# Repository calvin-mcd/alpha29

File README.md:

# alpha29

alpha29 (or mini planck) is a riff on the amazing [alpha28](https://github.com/PyrooL/Alpha) by PyrooL. This project was more of an exercise and is consider finished.

## Layout

[Link](https://www.keyboard-layout-editor.com/#/gists/f35a5c950e0317b4dc41fa3c3aa06123)

##RGB

Because this board uses a rp2040, you will need to use a logic shifter to utilise the rgb breakout. Something like [this](https://learn.sparkfun.com/tutorials/retired---using-the-logic-level-converter) or [this](https://learn.sparkfun.com/tutorials/bi-directional-logic-level-converter-hookup-guide) for example.

## Todo
- [ ] create firmware
- [ ] create case

## Disclaimer

Please note that this project is a work in progress with no guarantees of a working outcome. No-one involved in this project is responsible for any usage issues that may arise. However, feel free to edit, modify and otherwise utilise these files.

## License

This project is released under the GPL v3 License. Please refer to the LICENCE file.
  
## Credits

huge thanks to Pyrool for the inspiration.
  
Any questions, contact Calvin0563 on Discord.

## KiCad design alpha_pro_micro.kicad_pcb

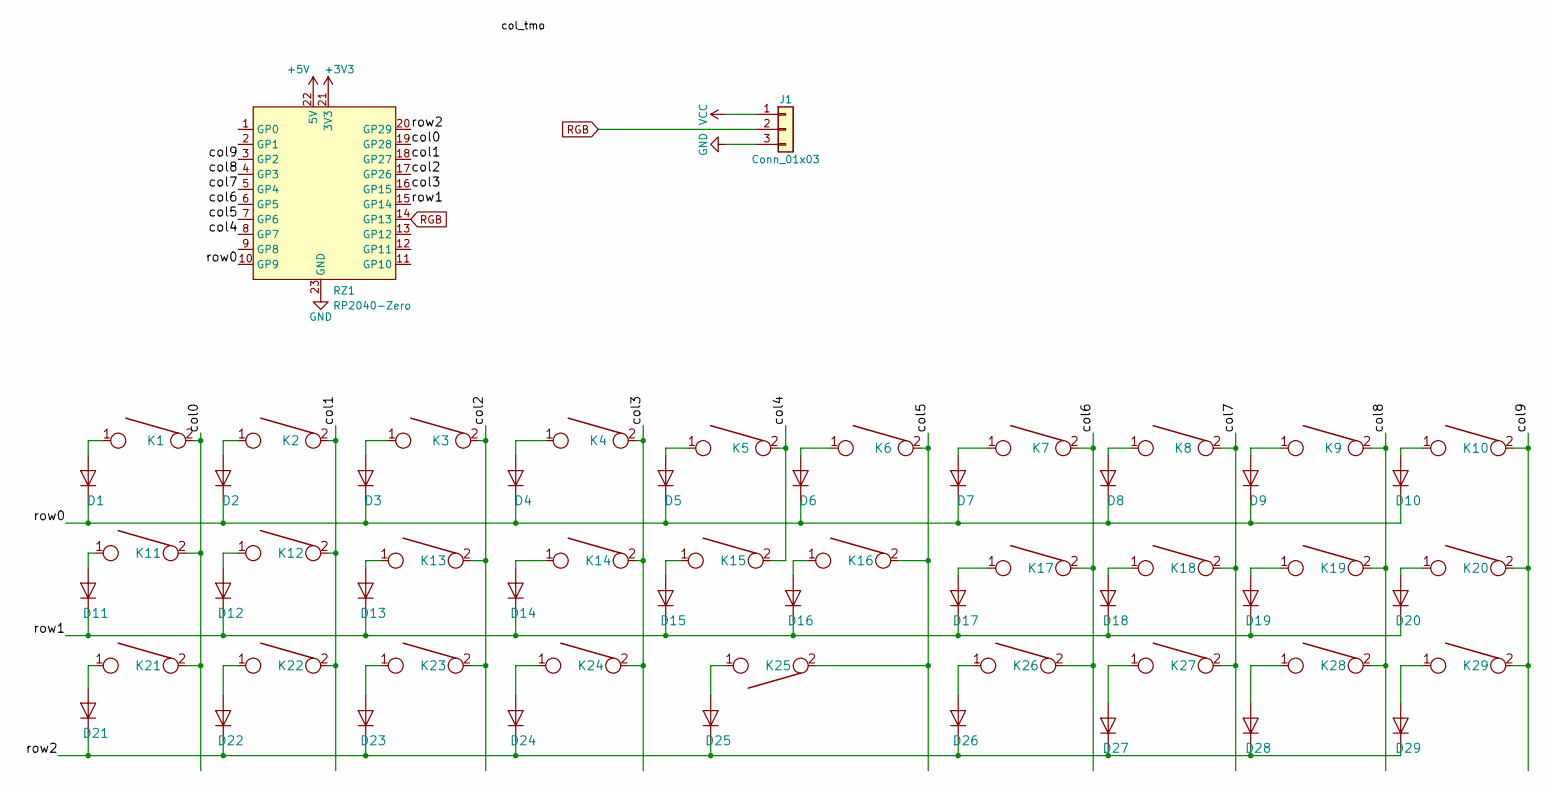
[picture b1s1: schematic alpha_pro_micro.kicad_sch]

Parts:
D1, D2, D3, D4, D5, D6, D7, D8, D9, D10, D11, D12, D13, D14, D15, D16, D17, D18, D19, D20, D21, D22, D23, D24, D25, D26, D27, D28, D29: D; ComboDiode
J1: Conn_01x03; Pin_Header_Straight_1x03_Pitch2.54mm
K1, K2, K3, K4, K5, K6, K7, K8, K9, K10, K11, K12, K13, K14, K15, K16, K17, K18, K19, K20, K21, K22, K23, K24, K26, K27, K28, K29: KEYSW; MXOnly-1U-NoLED
K25: KEYSW; MXOnly-2U-ReversedStabilizers-NoLED
RZ1: RP2040-Zero

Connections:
+3V3: RZ1.21 (3V3)
+5V: RZ1.22 (5V)
/col0: K1.2, K11.2, K21.2, RZ1.19 (GP28)
/col1: K2.2, K12.2, K22.2, RZ1.18 (GP27)
/col2: K3.2, K13.2, K23.2, RZ1.17 (GP26)
/col3: K4.2, K14.2, K24.2, RZ1.16 (GP15)
/col4: K5.2, K15.2, RZ1.8 (GP7)
/col5: K6.2, K16.2, K25.2, RZ1.7 (GP6)
/col6: K7.2, K17.2, K26.2, RZ1.6 (GP5)
/col7: K8.2, K18.2, K27.2, RZ1.5 (GP4)
/col8: K9.2, K19.2, K28.2, RZ1.4 (GP3)
/col9: K10.2, K20.2, K29.2, RZ1.3 (GP2)
/row0: D1.1 (K), D2.1 (K), D3.1 (K), D4.1 (K), D5.1 (K), D6.1 (K), D7.1 (K), D8.1 (K), D9.1 (K), D10.1 (K), RZ1.10 (GP9)
/row1: D11.1 (K), D12.1 (K), D13.1 (K), D14.1 (K), D15.1 (K), D16.1 (K), D17.1 (K), D18.1 (K), D19.1 (K), D20.1 (K), RZ1.15 (GP14)
/row2: D21.1 (K), D22.1 (K), D23.1 (K), D24.1 (K), D25.1 (K), D26.1 (K), D27.1 (K), D28.1 (K), D29.1 (K), RZ1.20 (GP29)
GND: J1.3, RZ1.23 (GND)
unnamed: D1.2 (A), K1.1
unnamed: D2.2 (A), K2.1
unnamed: D3.2 (A), K3.1
unnamed: D4.2 (A), K4.1
unnamed: D5.2 (A), K5.1
unnamed: D6.2 (A), K6.1
unnamed: D7.2 (A), K7.1
unnamed: D8.2 (A), K8.1
unnamed: D9.2 (A), K9.1
unnamed: D10.2 (A), K10.1
unnamed: D11.2 (A), K11.1
unnamed: D12.2 (A), K12.1
unnamed: D13.2 (A), K13.1
unnamed: D14.2 (A), K14.1
unnamed: D15.2 (A), K15.1
unnamed: D16.2 (A), K16.1
unnamed: D17.2 (A), K17.1
unnamed: D18.2 (A), K18.1
unnamed: D19.2 (A), K19.1
unnamed: D20.2 (A), K20.1
unnamed: D21.2 (A), K21.1
unnamed: D22.2 (A), K22.1
unnamed: D23.2 (A), K23.1
unnamed: D24.2 (A), K24.1
unnamed: D26.2 (A), K26.1
unnamed: D27.2 (A), K27.1
unnamed: D28.2 (A), K28.1
unnamed: D29.2 (A), K29.1
unnamed: D25.2 (A), K25.1
RGB: J1.2, RZ1.14 (GP13)
VCC: J1.1

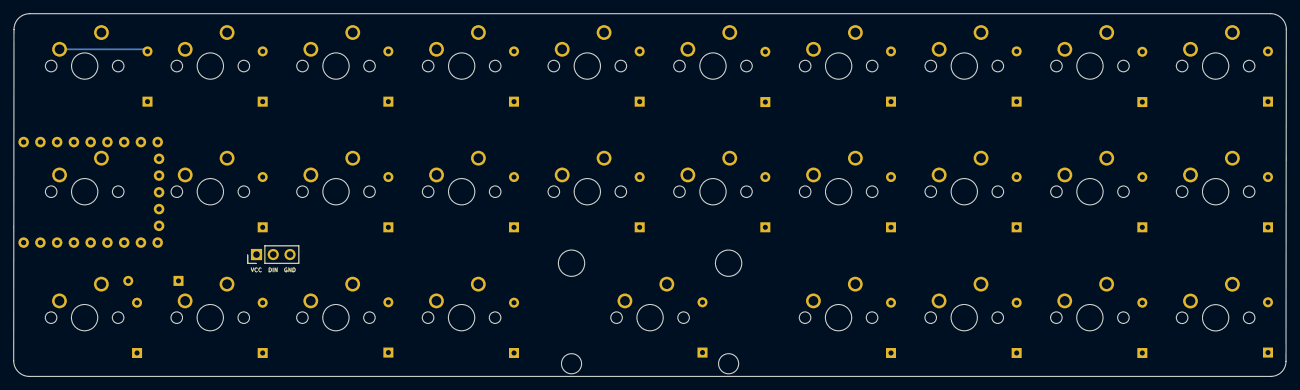
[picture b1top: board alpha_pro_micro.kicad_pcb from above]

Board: 2 copper layers, 192.9 x 55.0 mm, 60 parts (1 on the bottom side), 44 nets.

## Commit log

2022-12-12 footprints, routing
2022-12-16 alpha29 completed, but untested
2022-12-17 clean up
2022-12-31 backup
2023-01-10 readme
2023-01-15 clean up routing
2024-01-19 small update
